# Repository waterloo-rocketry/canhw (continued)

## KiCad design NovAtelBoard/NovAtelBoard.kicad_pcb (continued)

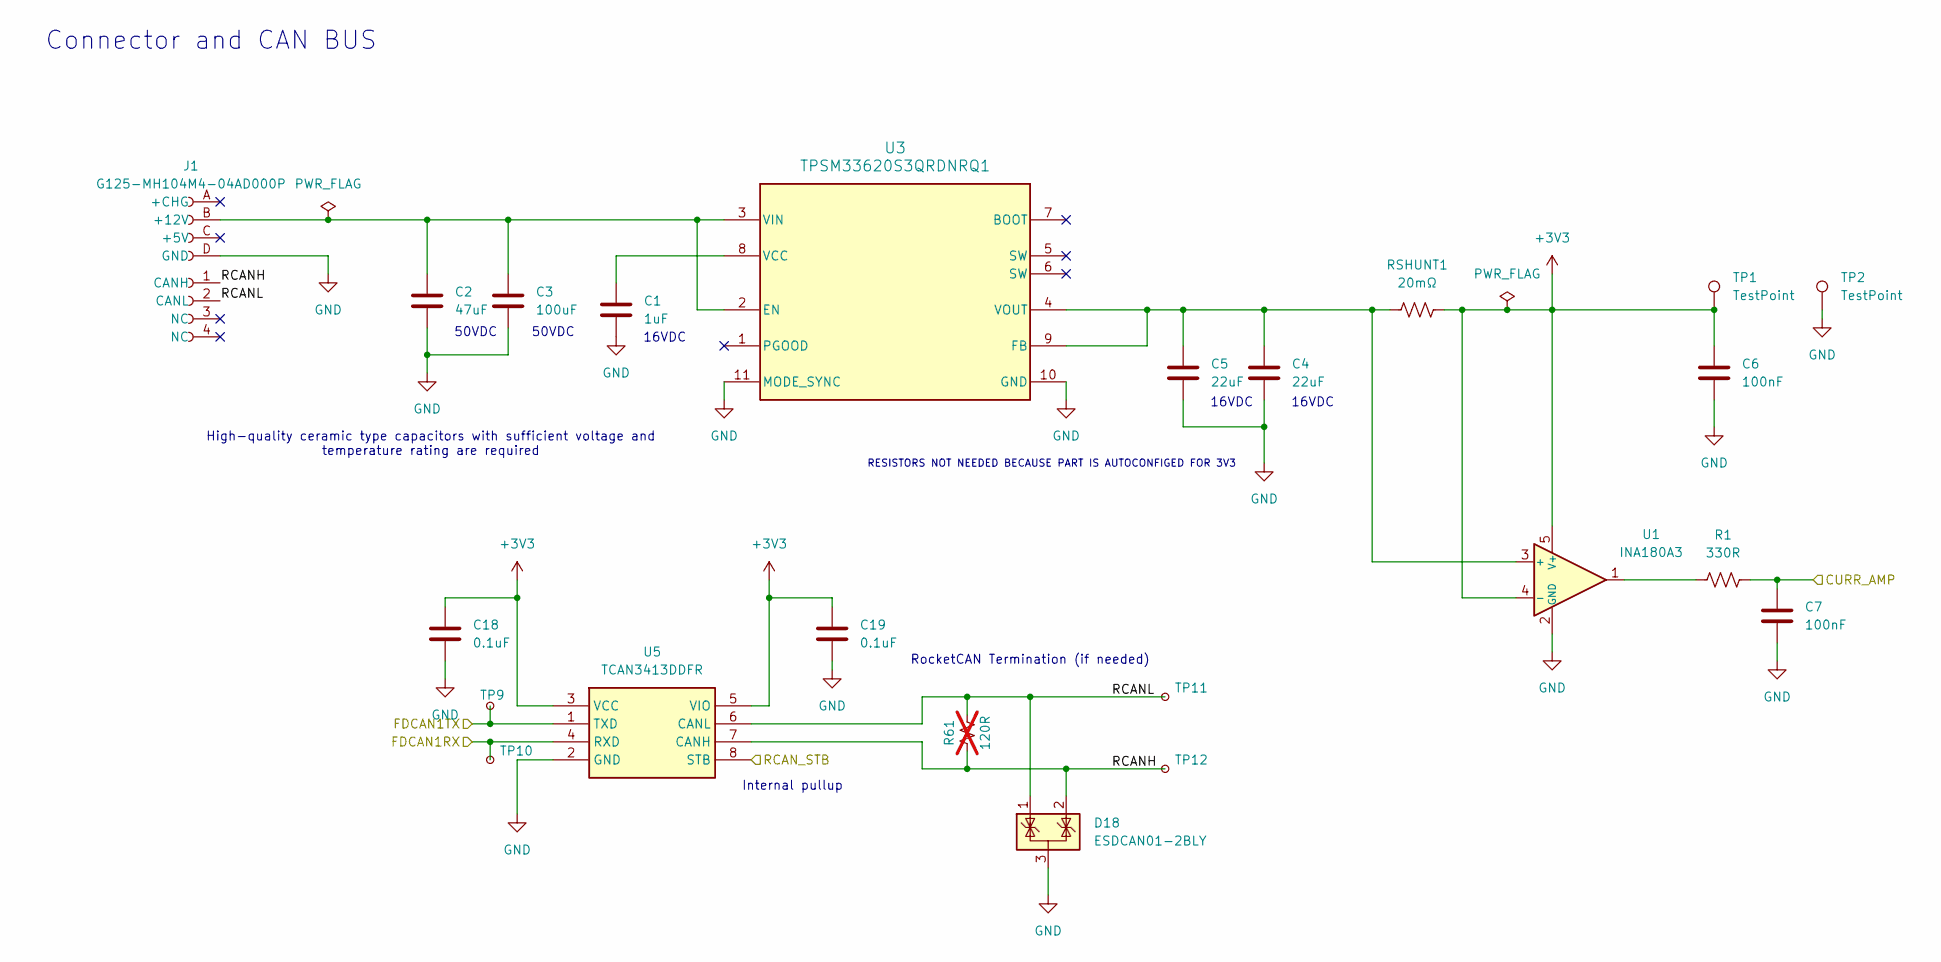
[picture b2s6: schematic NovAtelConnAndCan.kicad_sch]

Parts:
C1: 1uF; C_0603_1608Metric_Pad1.08x0.95mm_HandSolder
C2: 47uF; C_0603_1608Metric_Pad1.08x0.95mm_HandSolder
C3: 100uF; C_0603_1608Metric_Pad1.08x0.95mm_HandSolder
C4, C5: 22uF; C_0603_1608Metric_Pad1.08x0.95mm_HandSolder
C6, C7: 100nF; C_0603_1608Metric_Pad1.08x0.95mm_HandSolder
C18, C19: 0.1uF; C_0603_1608Metric_Pad1.08x0.95mm_HandSolder
D18: ESDCAN01-2BLY; SOT-23; LCSC Part # C1976606
J1: G125-MH104M4-04AD000P; connector_Harwin_G125–MG10605M4P
R1: 330R; DIP-8_W7.62mm
R61: 120R; R_0805_2012Metric; not fitted
RSHUNT1: 20mΩ; DIP-8_W7.62mm
TP1, TP2: TestPoint; SOT-23-5
TP9: RCAN_TX; TestPoint_Pad_D1.0mm
TP10: RCAN_RX; TestPoint_Pad_D1.0mm
TP11: RCAN_L; TestPoint_Pad_D1.0mm
TP12: RCAN_H; TestPoint_Pad_D1.0mm
U1: INA180A3; SOT-23-5
U3: TPSM33620S3QRDNRQ1; RDN0011B-MFG
U5: TCAN3413DDFR; Mouser Part Number 595-TCAN3413DDFR

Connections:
+3V3: C6.1, C18.1, C19.1, RSHUNT1.2, TP1.1 (1_1), U1.4 (-), U1.5 (V+), U5.3 (VCC), U5.5 (VIO); also elsewhere on the board
/NovAtelConnAndCan/CURR_AMP: C7.1, R1.2; also elsewhere on the board
/NovAtelConnAndCan/FDCAN1RX: TP10.1 (1_1), U5.4 (RXD); also elsewhere on the board
/NovAtelConnAndCan/FDCAN1TX: TP9.1 (1_1), U5.1 (TXD); also elsewhere on the board
/NovAtelConnAndCan/RCANH: D18.2 (K), J1.1 (CANH), R61.2, TP12.1 (1_1), U5.7 (CANH)
/NovAtelConnAndCan/RCANL: D18.1 (K), J1.2 (CANL), R61.1, TP11.1 (1_1), U5.6 (CANL)
/NovAtelConnAndCan/RCAN_STB: U5.8 (STB); also elsewhere on the board
GND: C1.2, C2.2, C3.2, C4.1, C5.2, C6.2, C7.2, C18.2, C19.2, D18.3 (A), J1.D (GND), TP2.1 (1_1), U1.2 (GND), U3.10 (GND), U3.11 (MODE_SYNC), U5.2 (GND); also elsewhere on the board
unnamed: C2.1, C3.1, J1.B (+12V), U3.2 (EN), U3.3 (VIN)
unnamed: R1.1, U1.1
unnamed: C4.2, C5.1, RSHUNT1.1, U1.3 (+), U3.4 (VOUT), U3.9 (FB)
unnamed: C1.1, U3.8 (VCC)

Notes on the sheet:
50VDC
16VDC
16VDC
High-quality ceramic type capacitors with sufficient voltage and temperature rating are required
Connector and CAN BUS
RocketCAN Termination (if needed)
Internal pullup
RESISTORS NOT NEEDED BECAUSE PART IS AUTOCONFIGED FOR 3V3

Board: 2 copper layers, 52 parts (0 on the bottom side), 32 nets, no tracks yet.

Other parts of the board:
J2: OEM719 Header Reciever; PinSocket_2x10_P2.54mm_Vertical

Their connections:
+3V3: J2.2 (3V3); also elsewhere on the board
/NovAtelHeader/OEM719PPS: J2.19 (PPS); also elsewhere on the board
/NovAtelHeader/OEM719_PV: J2.17 (PV); also elsewhere on the board
/NovAtelHeader/OEM719_RX: J2.12 (RXD1); also elsewhere on the board
/NovAtelHeader/OEM719_TX: J2.11 (TXD1); also elsewhere on the board
/NovAtelHeader/~OEM719_RESET: J2.5 (nRESET_IN); also elsewhere on the board
GND: J2.10 (GND), J2.13 (GND), J2.16 (GND), J2.18 (GND); also elsewhere on the board

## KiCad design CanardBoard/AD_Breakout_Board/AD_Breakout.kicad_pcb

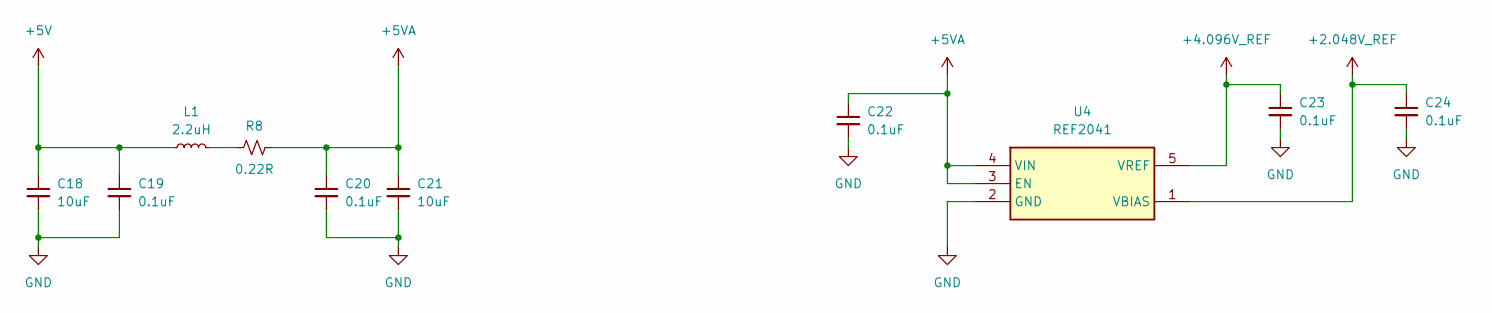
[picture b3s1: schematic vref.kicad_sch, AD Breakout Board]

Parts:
C18, C21: 10uF; C_0805_2012Metric
C19, C20, C22, C23, C24: 0.1uF; C_0402_1005Metric
L1: 2.2uH; L_1008_2520Metric; MPN LQM2HPN2R2MG0L
R8: 0.22R; R_0603_1608Metric
U4: REF2041; Mouser Part Number 595-REF2041AIDDCR

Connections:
+2.048V_REF: C24.1, U4.1 (VBIAS); also elsewhere on the board
+4.096V_REF: C23.1, U4.5 (VREF); also elsewhere on the board
+5V: C18.1, C19.1, L1.1; also elsewhere on the board
+5VA: C20.1, C21.1, C22.1, R8.2, U4.3 (EN), U4.4 (VIN); also elsewhere on the board
GND: C18.2, C19.2, C20.2, C21.2, C22.2, C23.2, C24.2, U4.2 (GND); also elsewhere on the board
unnamed: L1.2, R8.1

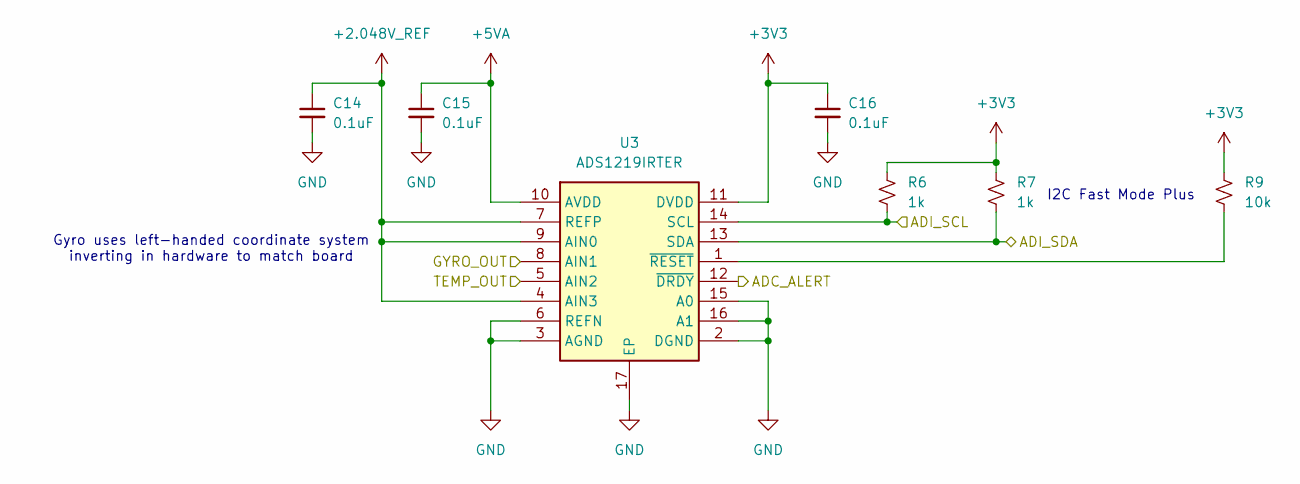
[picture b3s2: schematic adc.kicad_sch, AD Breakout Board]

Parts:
C14, C15, C16: 0.1uF; C_0402_1005Metric
R6, R7: 1k; R_0402_1005Metric
R9: 10k; R_0402_1005Metric
U3: ADS1219IRTER; Manufacturer_Part_Number ADS1219IRTER

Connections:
+2.048V_REF: C14.1, U3.4 (AIN3), U3.7 (REFP), U3.9 (AIN0); also elsewhere on the board
+3V3: C16.1, R6.1, R7.1, R9.1, U3.11 (DVDD); also elsewhere on the board
+5VA: C15.1, U3.10 (AVDD); also elsewhere on the board
/ADC/ADC_ALERT: U3.12 (~DRDY); also elsewhere on the board
/ADC/ADI_SCL: R6.2, U3.14 (SCL); also elsewhere on the board
/ADC/ADI_SDA: R7.2, U3.13 (SDA); also elsewhere on the board
/ADC/GYRO_OUT: U3.8 (AIN1); also elsewhere on the board
/ADC/TEMP_OUT: U3.5 (AIN2); also elsewhere on the board
GND: C14.2, C15.2, C16.2, U3.2 (DGND), U3.3 (AGND), U3.6 (REFN), U3.15 (A0), U3.16 (A1), U3.17 (EP); also elsewhere on the board
unnamed: R9.2, U3.1 (~RESET)

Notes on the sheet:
I2C Fast Mode Plus
Gyro uses left-handed coordinate system inverting in hardware to match board

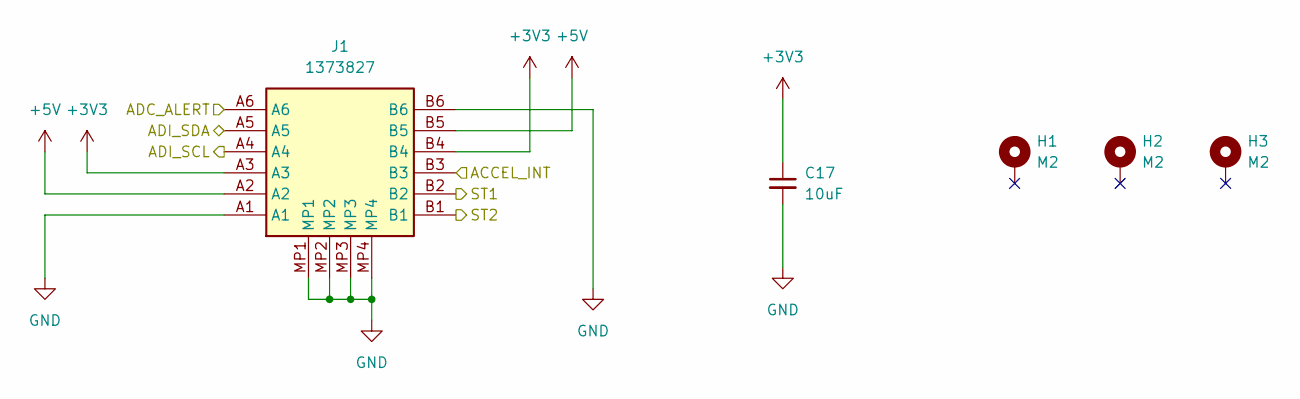
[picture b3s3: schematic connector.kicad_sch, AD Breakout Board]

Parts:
C17: 10uF; C_0805_2012Metric
H1, H2, H3: M2; MountingHole_2.2mm_M2_Pad
J1: 1373827; Mouser Part Number 651-1373827

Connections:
+3V3: C17.1, J1.A3, J1.B4; also elsewhere on the board
+5V: J1.A2, J1.B5; also elsewhere on the board
/ADC/ADC_ALERT: J1.A6; also elsewhere on the board
/ADC/ADI_SCL: J1.A4; also elsewhere on the board
/ADC/ADI_SDA: J1.A5; also elsewhere on the board
/Accelerometer/ACCEL_INT: J1.B3; also elsewhere on the board
/ST1: J1.B2; also elsewhere on the board
/ST2: J1.B1; also elsewhere on the board
GND: C17.2, J1.A1, J1.B6, J1.MP1, J1.MP2, J1.MP3, J1.MP4; also elsewhere on the board

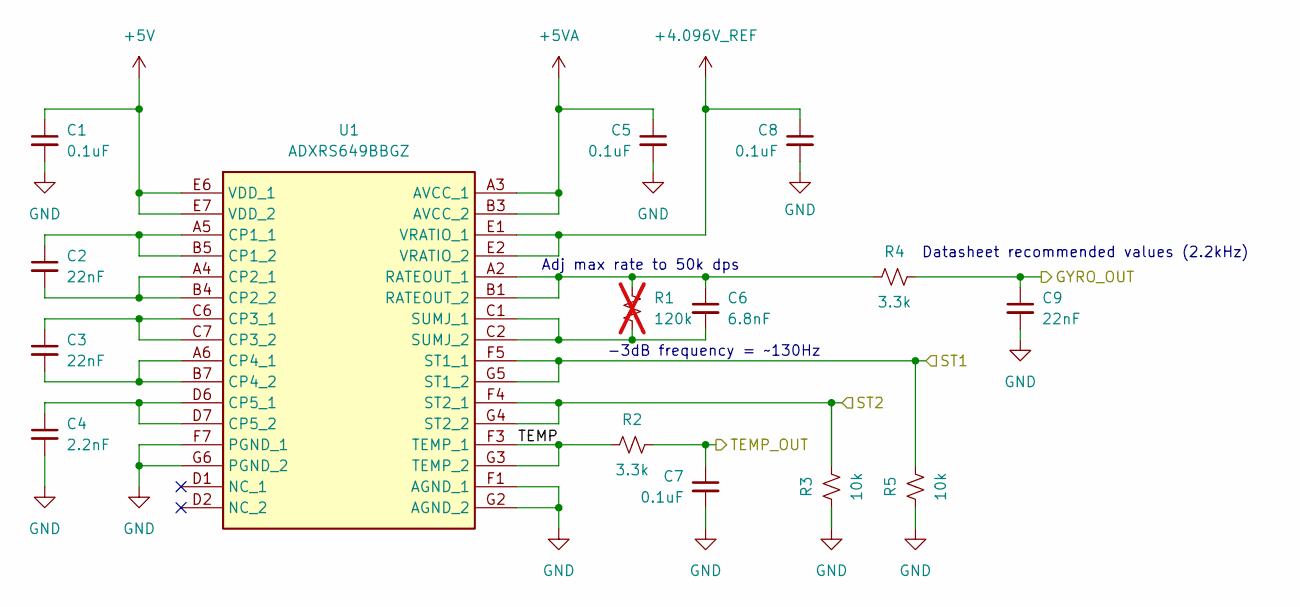
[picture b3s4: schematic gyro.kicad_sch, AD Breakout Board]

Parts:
C1, C5, C7, C8: 0.1uF; C_0402_1005Metric
C2, C3, C9: 22nF; C_0402_1005Metric
C4: 2.2nF; C_0402_1005Metric
C6: 6.8nF; C_0402_1005Metric
R1: 120k; R_0402_1005Metric; not fitted
R2, R4: 3.3k; R_0402_1005Metric
R3, R5: 10k; R_0402_1005Metric
U1: ADXRS649BBGZ; Mouser Part Number N/A

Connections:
+4.096V_REF: C8.1, U1.E1 (VRATIO_1), U1.E2 (VRATIO_2); also elsewhere on the board
+5V: C1.1, U1.E6 (VDD_1), U1.E7 (VDD_2); also elsewhere on the board
+5VA: C5.1, U1.A3 (AVCC_1), U1.B3 (AVCC_2); also elsewhere on the board
/ADC/GYRO_OUT: C9.1, R4.2; also elsewhere on the board
/ADC/TEMP_OUT: C7.1, R2.2; also elsewhere on the board
/Gyroscope/TEMP: R2.1, U1.F3 (TEMP_1), U1.G3 (TEMP_2)
/ST1: R5.2, U1.F5 (ST1_1), U1.G5 (ST1_2); also elsewhere on the board
/ST2: R3.2, U1.F4 (ST2_1), U1.G4 (ST2_2); also elsewhere on the board
GND: C1.2, C4.2, C5.2, C7.2, C8.2, C9.2, R3.1, R5.1, U1.F1 (AGND_1), U1.F7 (PGND_1), U1.G2 (AGND_2), U1.G6 (PGND_2); also elsewhere on the board
unnamed: C2.1, U1.A5 (CP1_1), U1.B5 (CP1_2)
unnamed: C2.2, U1.A4 (CP2_1), U1.B4 (CP2_2)
unnamed: C3.1, U1.C6 (CP3_1), U1.C7 (CP3_2)
unnamed: C3.2, U1.A6 (CP4_1), U1.B7 (CP4_2)
unnamed: C4.1, U1.D6 (CP5_1), U1.D7 (CP5_2)
unnamed: C6.1, R1.2, R4.1, U1.A2 (RATEOUT_1), U1.B1 (RATEOUT_2)
unnamed: C6.2, R1.1, U1.C1 (SUMJ_1), U1.C2 (SUMJ_2)

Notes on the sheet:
-3dB frequency = ~130Hz
Datasheet recommended values (2.2kHz)
Adj max rate to 50k dps

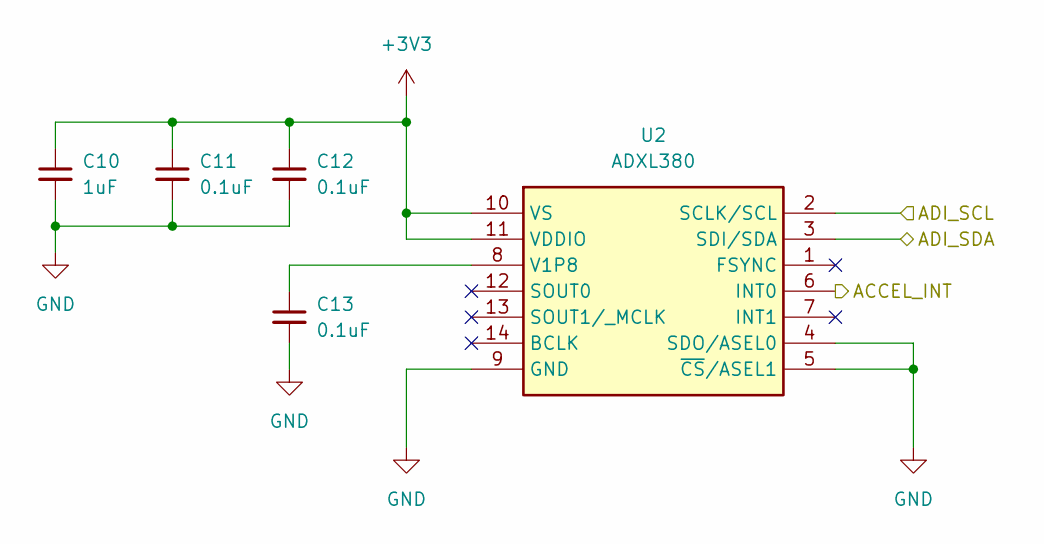
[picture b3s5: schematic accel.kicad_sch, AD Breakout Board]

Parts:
C10: 1uF; C_0402_1005Metric
C11, C12, C13: 0.1uF; C_0402_1005Metric
U2: ADXL380; Mouser Part Number 584-ADXL380-1BCCZRL7

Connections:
+3V3: C10.1, C11.1, C12.1, U2.10 (VS), U2.11 (VDDIO); also elsewhere on the board
/ADC/ADI_SCL: U2.2 (SCLK/SCL); also elsewhere on the board
/ADC/ADI_SDA: U2.3 (SDI/SDA); also elsewhere on the board
/Accelerometer/ACCEL_INT: U2.6 (INT0); also elsewhere on the board
GND: C10.2, C11.2, C12.2, C13.2, U2.4 (SDO/ASEL0), U2.5 (~CS/ASEL1), U2.9 (GND); also elsewhere on the board
unnamed: C13.1, U2.8 (V1P8)

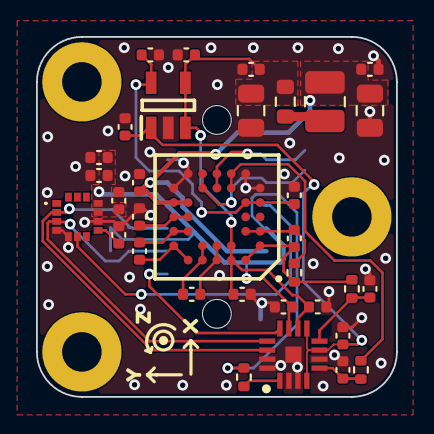
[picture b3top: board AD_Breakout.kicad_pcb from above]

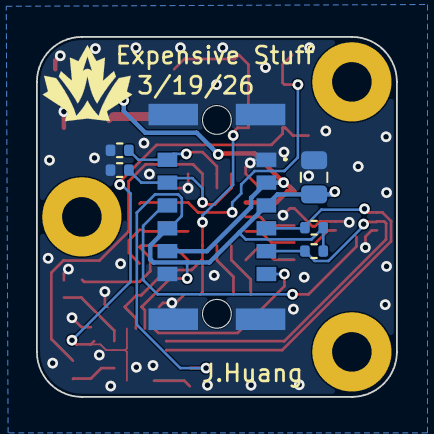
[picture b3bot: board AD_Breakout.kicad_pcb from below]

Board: 4 copper layers, 20.0 x 20.0 mm, 42 parts (6 on the bottom side), 25 nets.

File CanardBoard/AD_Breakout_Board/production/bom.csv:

Designator,Footprint,Quantity,Value,LCSC Part #
"C1, C11, C12, C13, C14, C15, C16, C19, C20, C22, C23, C24, C5, C7, C8",0402,15,0.1uF,
C10,0402,1,1uF,
"C17, C18, C21",0805,3,10uF,
"C2, C3, C9",0402,3,22nF,
C4,0402,1,2.2nF,
C6,0402,1,6.8nF,
J1,1373827,1,1373827,
L1,1008,1,2.2uH,LQM2HPN2R2MG0L
R1,0402,1,120k,
"R2, R4",0402,2,3.3k,
"R3, R5, R9",0402,3,10k,
"R6, R7",0402,2,1k,
R8,0603,1,0.22R,
U1,ADXRS649BBGZ,1,ADXRS649BBGZ,
U2,ADXL380,1,ADXL380,
U3,ADS1219IRTER,1,ADS1219IRTER,
U4,REF2041,1,REF2041,

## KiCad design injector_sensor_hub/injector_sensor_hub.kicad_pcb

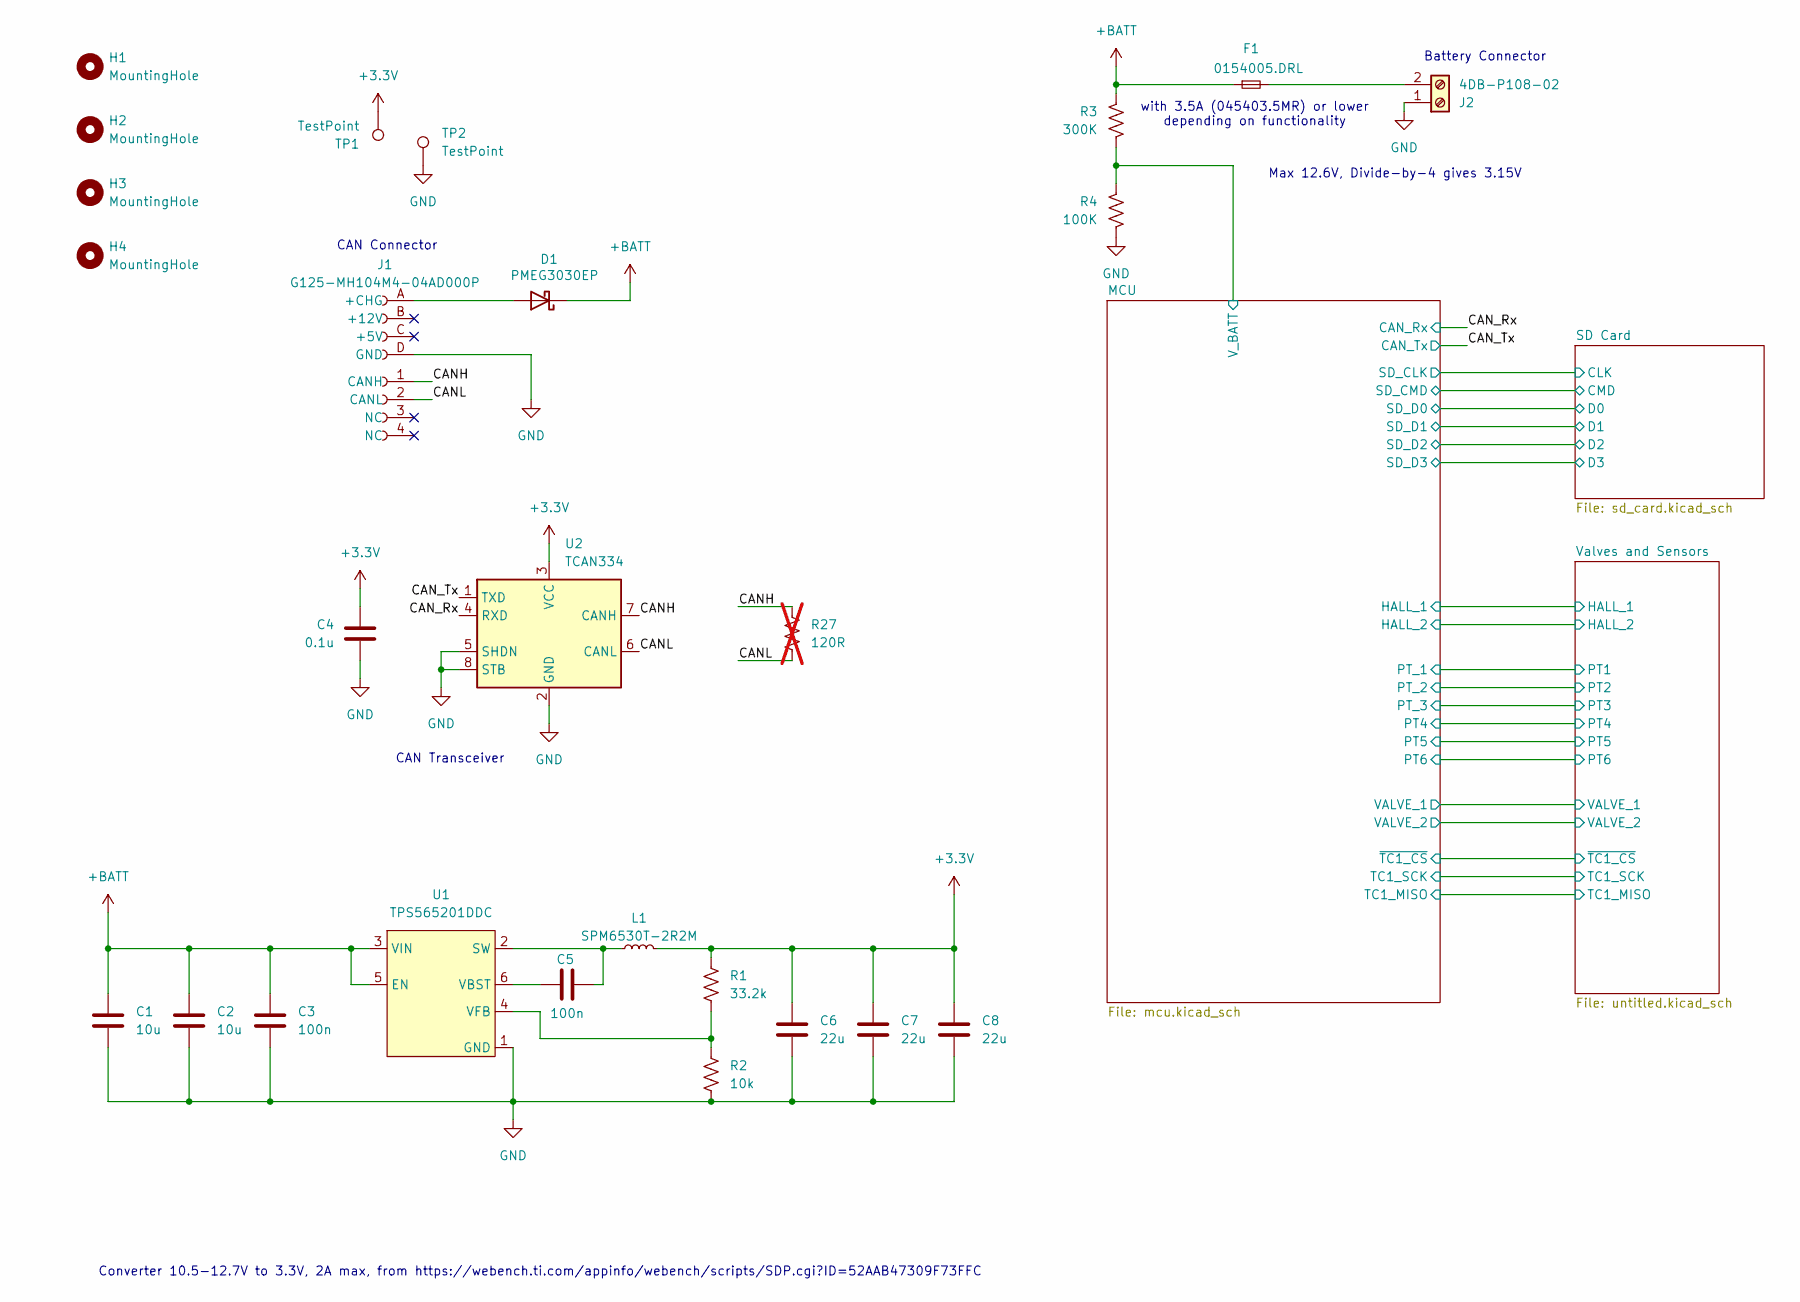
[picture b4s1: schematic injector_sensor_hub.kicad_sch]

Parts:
C1, C2: 10u; C_0603_1608Metric_Pad1.08x0.95mm_HandSolder
C3, C5: 100n; C_0603_1608Metric_Pad1.08x0.95mm_HandSolder
C4: 0.1u; C_0603_1608Metric_Pad1.08x0.95mm_HandSolder
C6, C7, C8: 22u; C_0603_1608Metric_Pad1.08x0.95mm_HandSolder
D1: PMEG3030EP; D_SOD-128
F1: 0154005.DRL; FUSE_0154005.DR
H1, H2, H3, H4: MountingHole; MountingHole_3.2mm_M3_ISO14580
J1: G125-MH104M4-04AD000P; connector_Harwin_G125-MH104M4-04AD000P
J2: 4DB-P108-02
L1: SPM6530T-2R2M; IND_SPM6530T-2R2M
R1: 33.2k; R_0603_1608Metric_Pad0.98x0.95mm_HandSolder
R2: 10k; R_0603_1608Metric_Pad0.98x0.95mm_HandSolder
R3: 300K; R_0603_1608Metric_Pad0.98x0.95mm_HandSolder
R4: 100K; R_0603_1608Metric_Pad0.98x0.95mm_HandSolder
R27: 120R; R_0603_1608Metric_Pad0.98x0.95mm_HandSolder; not fitted
TP1: TestPoint; TestPoint_Pad_D2.0mm
TP2: TestPoint; TestPoint_Keystone_5000-5004_Miniature
U1: TPS565201DDC; SOT-23-6_Handsoldering
U2: TCAN334; SOIC-8_3.9x4.9mm_P1.27mm

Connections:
+3.3V: C4.1, C6.1, C7.1, C8.1, L1.1, R1.1, TP1.1, U2.3 (VCC); also elsewhere on the board
+BATT: C1.1, C2.1, C3.1, D1.1 (K), F1.1, R3.1, U1.3 (VIN), U1.5 (EN); also elsewhere on the board
/CANH: J1.1 (CANH), R27.1, U2.7 (CANH)
/CANL: J1.2 (CANL), R27.2, U2.6 (CANL)
/CAN_Rx: U2.4 (RXD); also elsewhere on the board
/CAN_Tx: U2.1 (TXD); also elsewhere on the board
/MCU/V_BATT: R3.2, R4.1; also elsewhere on the board
GND: C1.2, C2.2, C3.2, C4.2, C6.2, C7.2, C8.2, J1.D (GND), J2.1, R2.2, R4.2, TP2.1, U1.1 (GND), U2.2 (GND), U2.5 (SHDN), U2.8 (STB); also elsewhere on the board
unnamed: D1.2 (A), J1.A (+CHG)
unnamed: F1.2, J2.2
unnamed: C5.1, L1.2, U1.2 (SW)
unnamed: C5.2, U1.6 (VBST)
unnamed: R1.2, R2.1, U1.4 (VFB)

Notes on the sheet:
Converter 10.5-12.7V to 3.3V, 2A max, from https://webench.ti.com/appinfo/webench/scripts/SDP.cgi?ID=52AAB47309F73FFC
Max 12.6V, Divide-by-4 gives 3.15V
with 3.5A (045403.5MR) or lower depending on functionality
CAN Connector
Battery Connector
CAN Transceiver

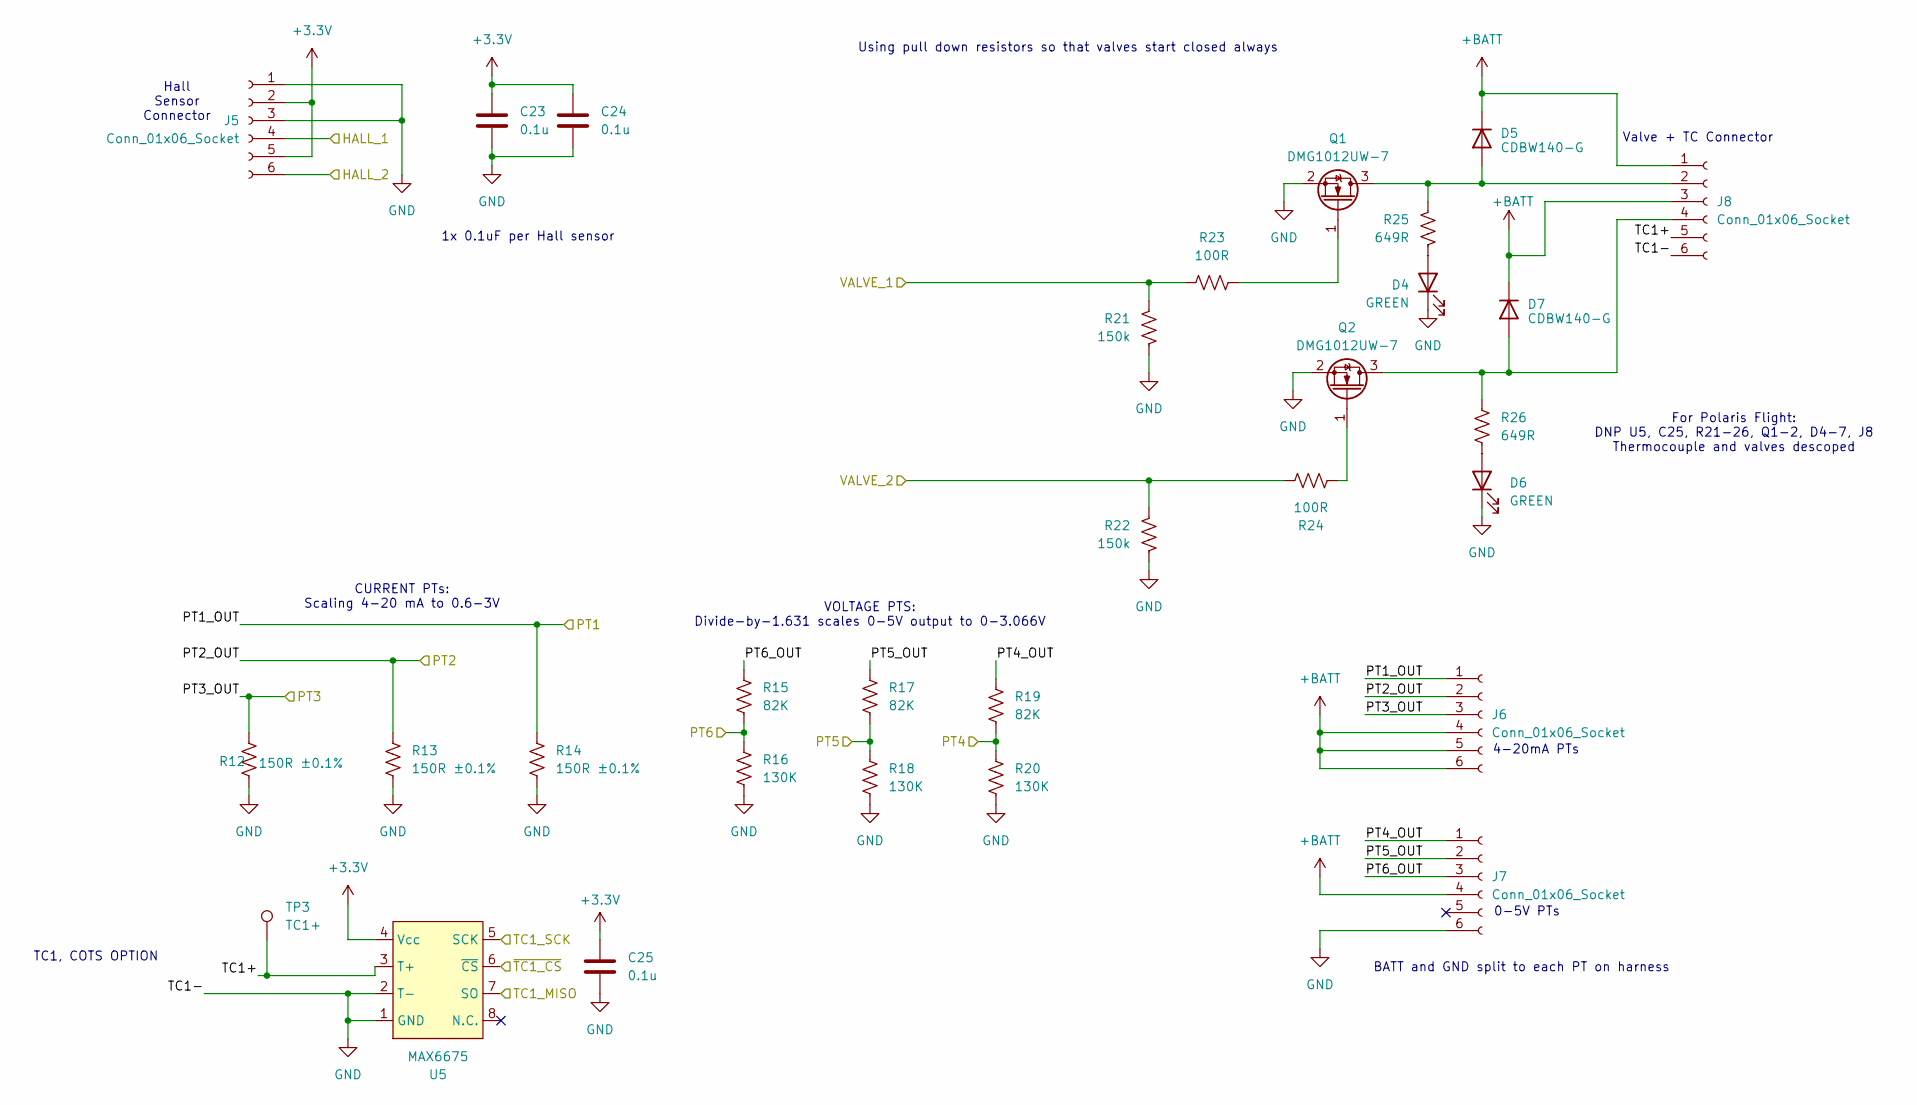
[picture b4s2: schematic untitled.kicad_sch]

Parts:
C23, C24, C25: 0.1u; C_0603_1608Metric_Pad1.08x0.95mm_HandSolder
D4, D6: GREEN; LED_1206_3216Metric_Pad1.42x1.75mm_HandSolder
D5, D7: CDBW140-G; D_SOD-123
J5, J6, J7, J8: Conn_01x06_Socket; connector_Harwin_G125–MG10605M4P
Q1, Q2: DMG1012UW-7; SOT_12UW-7_DIO
R12, R13, R14: 150R ±0.1%; R_0603_1608Metric_Pad0.98x0.95mm_HandSolder
R15, R17, R19: 82K; R_0603_1608Metric_Pad0.98x0.95mm_HandSolder
R16, R18, R20: 130K; R_0603_1608Metric_Pad0.98x0.95mm_HandSolder
R21, R22: 150k; R_0603_1608Metric_Pad0.98x0.95mm_HandSolder
R23, R24: 100R; R_0603_1608Metric_Pad0.98x0.95mm_HandSolder
R25, R26: 649R; R_0603_1608Metric_Pad0.98x0.95mm_HandSolder
TP3: TC1+; TestPoint_Pad_D2.0mm
U5: MAX6675; SOIC-8_3.9x4.9mm_P1.27mm

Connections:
+3.3V: C23.1, C24.1, C25.1, J5.2, J5.5, U5.4 (Vcc); also elsewhere on the board
+BATT: D5.1 (K), D7.1 (K), J6.4, J6.5, J6.6, J7.4, J8.1, J8.3; also elsewhere on the board
/MCU/HALL_1: J5.4; also elsewhere on the board
/MCU/HALL_2: J5.6; also elsewhere on the board
/MCU/PT4: R19.2, R20.1; also elsewhere on the board
/MCU/PT5: R17.2, R18.1; also elsewhere on the board
/MCU/PT6: R15.2, R16.1; also elsewhere on the board
/MCU/TC1_MISO: U5.7 (SO); also elsewhere on the board
/MCU/TC1_SCK: U5.5 (SCK); also elsewhere on the board
/MCU/VALVE_1: R21.2, R23.2; also elsewhere on the board
/MCU/VALVE_2: R22.1, R24.2; also elsewhere on the board
/MCU/~TC1_CS: U5.6 (~CS); also elsewhere on the board
/Valves and Sensors/PT1_OUT: J6.1, R14.1; also elsewhere on the board
/Valves and Sensors/PT2_OUT: J6.2, R13.1; also elsewhere on the board
/Valves and Sensors/PT3_OUT: J6.3, R12.1; also elsewhere on the board
/Valves and Sensors/PT4_OUT: J7.1, R19.1
/Valves and Sensors/PT5_OUT: J7.2, R17.1
/Valves and Sensors/PT6_OUT: J7.3, R15.1
/Valves and Sensors/TC1+: J8.5, TP3.1, U5.3 (T+); also elsewhere on the board
GND: C23.2, C24.2, C25.2, D4.1 (K), D6.1 (K), J5.1, J5.3, J7.6, J8.6, Q1.2 (S), Q2.2 (S), R12.2, R13.2, R14.2, R16.2, R18.2, R20.2, R21.1, R22.2, U5.1 (GND), U5.2 (T-); also elsewhere on the board
unnamed: D4.2 (A), R25.1
unnamed: D5.2 (A), J8.2, Q1.3 (D), R25.2
unnamed: D6.2 (A), R26.2
unnamed: D7.2 (A), J8.4, Q2.3 (D), R26.1
unnamed: Q1.1 (G), R23.1
unnamed: Q2.1 (G), R24.1

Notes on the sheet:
Hall Sensor Connector
0-5V PTs
Valve + TC Connector
1x 0.1uF per Hall sensor
CURRENT PTs: Scaling 4-20 mA to 0.6-3V
For Polaris Flight: DNP U5, C25, R21-26, Q1-2, D4-7, J8 Thermocouple and valves descoped
BATT and GND split to each PT on harness
Using pull down resistors so that valves start closed always
4-20mA PTs
TC1, COTS OPTION
VOLTAGE PTS: Divide-by-1.631 scales 0-5V output to 0-3.066V

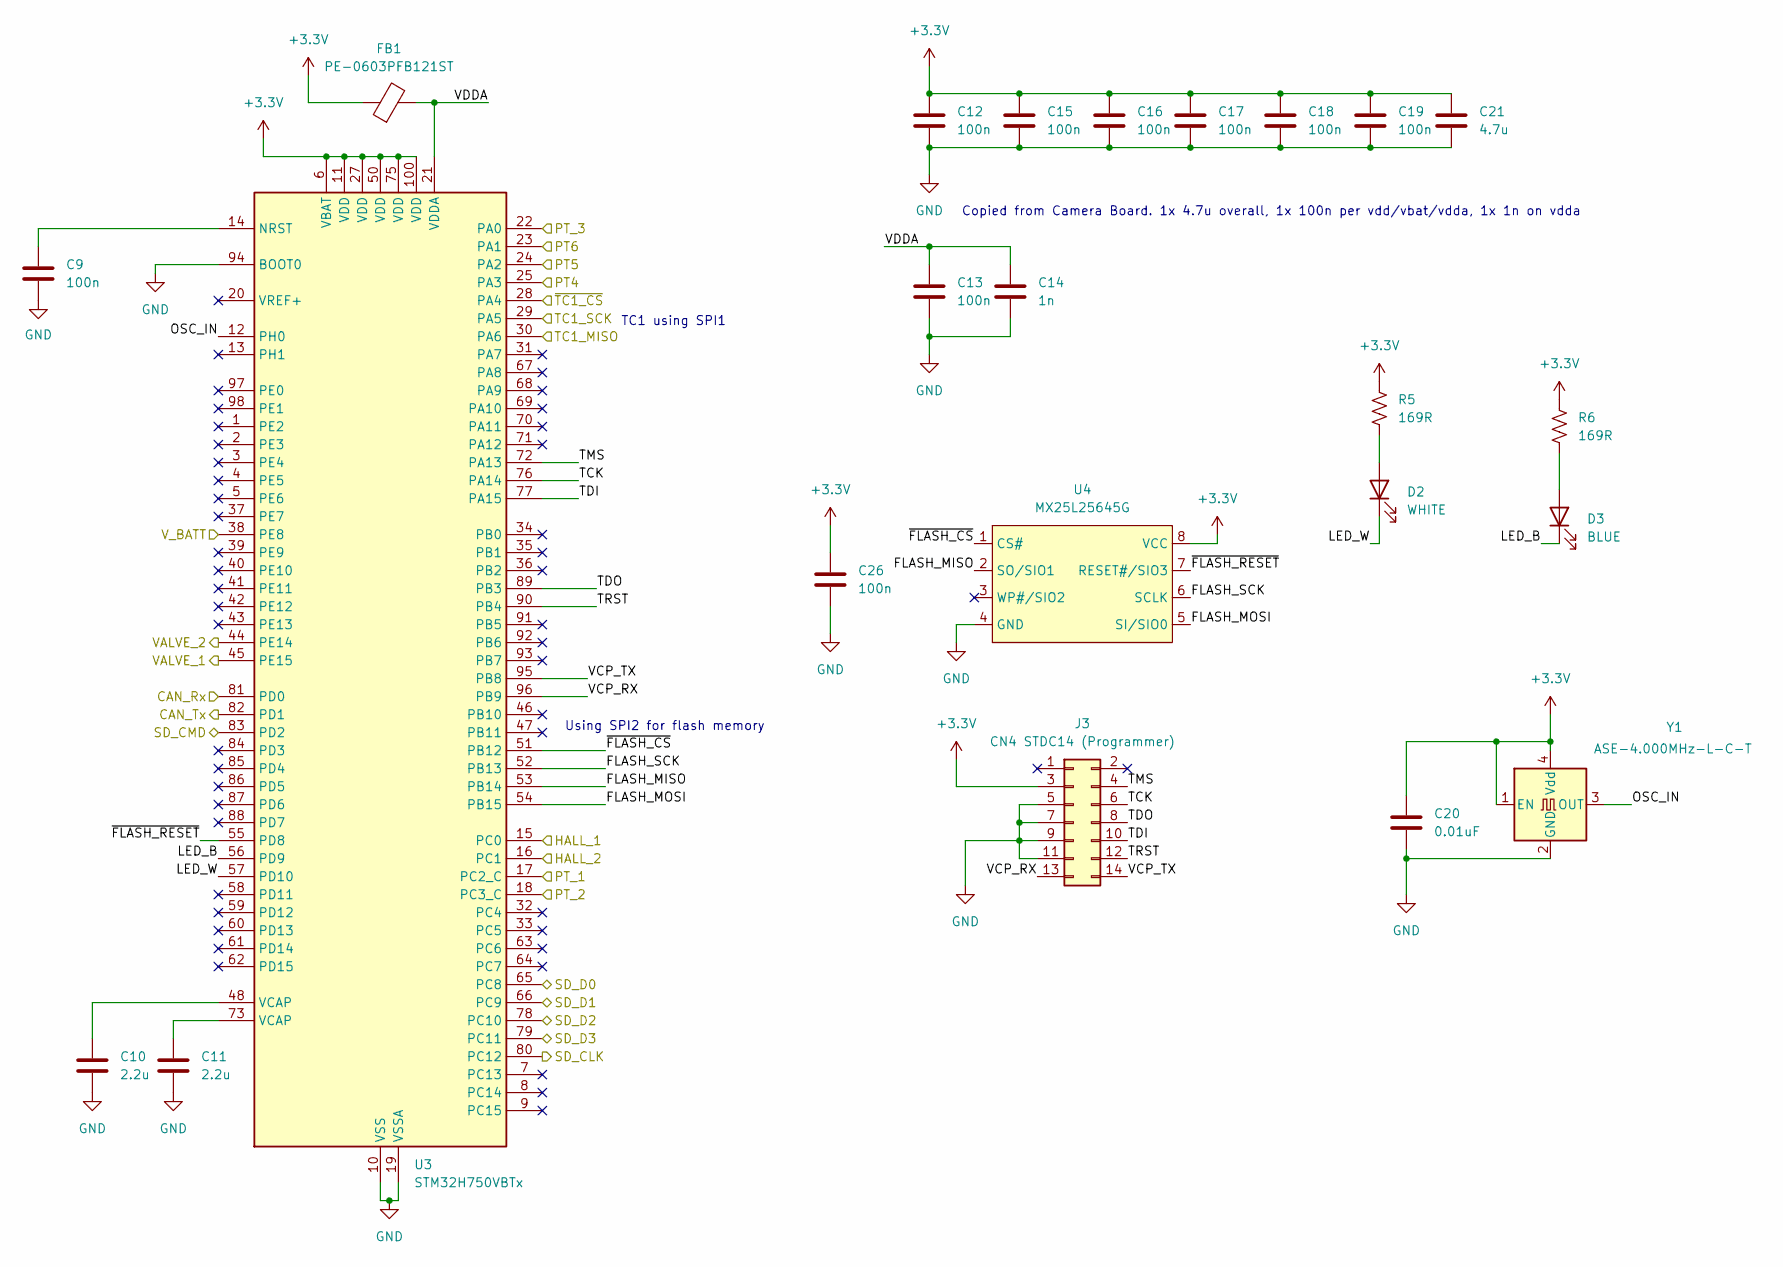
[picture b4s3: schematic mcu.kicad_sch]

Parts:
C9, C12, C13, C15, C16, C17, C18, C19, C26: 100n; C_0603_1608Metric_Pad1.08x0.95mm_HandSolder
C10, C11: 2.2u; C_0603_1608Metric_Pad1.08x0.95mm_HandSolder
C14: 1n; C_0603_1608Metric_Pad1.08x0.95mm_HandSolder
C20: 0.01uF; C_0603_1608Metric_Pad1.08x0.95mm_HandSolder
C21: 4.7u; C_0603_1608Metric_Pad1.08x0.95mm_HandSolder
D2: WHITE; LED_1206_3216Metric_Pad1.42x1.75mm_HandSolder
D3: BLUE; LED_1206_3216Metric_Pad1.42x1.75mm_HandSolder
FB1: PE-0603PFB121ST; R_0603_1608Metric_Pad0.98x0.95mm_HandSolder
J3: CN4 STDC14 (Programmer); PinSocket_2x07_P1.27mm_Vertical_SMD
R5, R6: 169R; R_0603_1608Metric_Pad0.98x0.95mm_HandSolder
U3: STM32H750VBTx; LQFP-100_14x14mm_P0.5mm
U4: MX25L25645G; SOIC-8_5.3x5.3mm_P1.27mm
Y1: ASE-4.000MHz-L-C-T; Oscillator_SMD_Abracon_ASE-4Pin_3.2x2.5mm

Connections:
+3.3V: C12.1, C15.1, C16.1, C17.1, C18.1, C19.1, C20.1, C21.1, C26.1, FB1.1, J3.3, R5.1, R6.1, U3.6 (VBAT), U3.11 (VDD), U3.27 (VDD), U3.50 (VDD), U3.75 (VDD), U3.100 (VDD), U4.8 (VCC), Y1.1 (EN), Y1.4 (Vdd); also elsewhere on the board
/CAN_Rx: U3.81 (PD0); also elsewhere on the board
/CAN_Tx: U3.82 (PD1); also elsewhere on the board
/MCU/FLASH_MISO: U3.53 (PB14), U4.2 (SO/SIO1)
/MCU/FLASH_MOSI: U3.54 (PB15), U4.5 (SI/SIO0)
/MCU/FLASH_SCK: U3.52 (PB13), U4.6 (SCLK)
/MCU/HALL_1: U3.15 (PC0); also elsewhere on the board
/MCU/HALL_2: U3.16 (PC1); also elsewhere on the board
/MCU/LED_B: D3.1 (K), U3.56 (PD9)
/MCU/LED_W: D2.1 (K), U3.57 (PD10)
/MCU/OSC_IN: U3.12 (PH0), Y1.3 (OUT)
/MCU/PT4: U3.25 (PA3); also elsewhere on the board
/MCU/PT5: U3.24 (PA2); also elsewhere on the board
/MCU/PT6: U3.23 (PA1); also elsewhere on the board
/MCU/SD_CLK: U3.80 (PC12); also elsewhere on the board
/MCU/SD_CMD: U3.83 (PD2); also elsewhere on the board
/MCU/SD_D0: U3.65 (PC8); also elsewhere on the board
/MCU/SD_D1: U3.66 (PC9); also elsewhere on the board
/MCU/SD_D2: U3.78 (PC10); also elsewhere on the board
/MCU/SD_D3: U3.79 (PC11); also elsewhere on the board
/MCU/TC1_MISO: U3.30 (PA6); also elsewhere on the board
/MCU/TC1_SCK: U3.29 (PA5); also elsewhere on the board
/MCU/TCK: J3.6, U3.76 (PA14)
/MCU/TDI: J3.10, U3.77 (PA15)
/MCU/TDO: J3.8, U3.89 (PB3)
/MCU/TMS: J3.4, U3.72 (PA13)
/MCU/TRST: J3.12, U3.90 (PB4)
/MCU/VALVE_1: U3.45 (PE15); also elsewhere on the board
/MCU/VALVE_2: U3.44 (PE14); also elsewhere on the board
/MCU/VCP_RX: J3.13, U3.96 (PB9)
/MCU/VCP_TX: J3.14, U3.95 (PB8)
/MCU/VDDA: C13.1, C14.1, FB1.2, U3.21 (VDDA)
/MCU/V_BATT: U3.38 (PE8); also elsewhere on the board
/MCU/~FLASH_CS: U3.51 (PB12), U4.1 (CS#)
/MCU/~FLASH_RESET: U3.55 (PD8), U4.7 (RESET#/SIO3)
/MCU/~TC1_CS: U3.28 (PA4); also elsewhere on the board
/Valves and Sensors/PT1_OUT: U3.17 (PC2_C); also elsewhere on the board
/Valves and Sensors/PT2_OUT: U3.18 (PC3_C); also elsewhere on the board
/Valves and Sensors/PT3_OUT: U3.22 (PA0); also elsewhere on the board
GND: C9.2, C10.2, C11.2, C12.2, C13.2, C14.2, C15.2, C16.2, C17.2, C18.2, C19.2, C20.2, C21.2, C26.2, J3.5, J3.7, J3.9, J3.11, U3.10 (VSS), U3.19 (VSSA), U3.26 (VSS), U3.49 (VSS), U3.74 (VSS), U3.94 (BOOT0), U3.99 (VSS), U4.4 (GND), Y1.2 (GND); also elsewhere on the board
unnamed: C10.1, U3.48 (VCAP)
unnamed: C11.1, U3.73 (VCAP)
unnamed: D2.2 (A), R5.2
unnamed: D3.2 (A), R6.2
unnamed: C9.1, U3.14 (NRST)

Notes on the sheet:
Using SPI2 for flash memory
TC1 using SPI1
Copied from Camera Board. 1x 4.7u overall, 1x 100n per vdd/vbat/vdda, 1x 1n on vdda

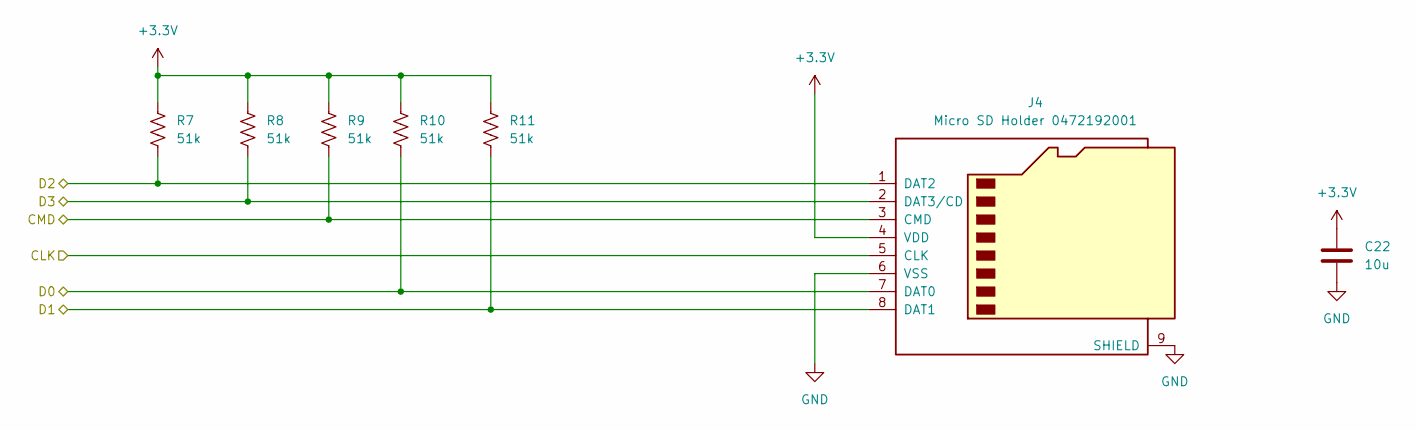
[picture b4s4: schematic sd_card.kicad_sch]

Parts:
C22: 10u; C_0603_1608Metric_Pad1.08x0.95mm_HandSolder
J4: Micro SD Holder 0472192001; microSD_HC_Molex_47219-2001
R7, R8, R9, R10, R11: 51k; R_0603_1608Metric_Pad0.98x0.95mm_HandSolder

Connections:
+3.3V: C22.1, J4.4 (VDD), R7.1, R8.1, R9.1, R10.1, R11.1; also elsewhere on the board
/MCU/SD_CLK: J4.5 (CLK); also elsewhere on the board
/MCU/SD_CMD: J4.3 (CMD), R9.2; also elsewhere on the board
/MCU/SD_D0: J4.7 (DAT0), R10.2; also elsewhere on the board
/MCU/SD_D1: J4.8 (DAT1), R11.2; also elsewhere on the board
/MCU/SD_D2: J4.1 (DAT2), R7.2; also elsewhere on the board
/MCU/SD_D3: J4.2 (DAT3/CD), R8.2; also elsewhere on the board
GND: C22.2, J4.6 (VSS), J4.9 (SHIELD); also elsewhere on the board
